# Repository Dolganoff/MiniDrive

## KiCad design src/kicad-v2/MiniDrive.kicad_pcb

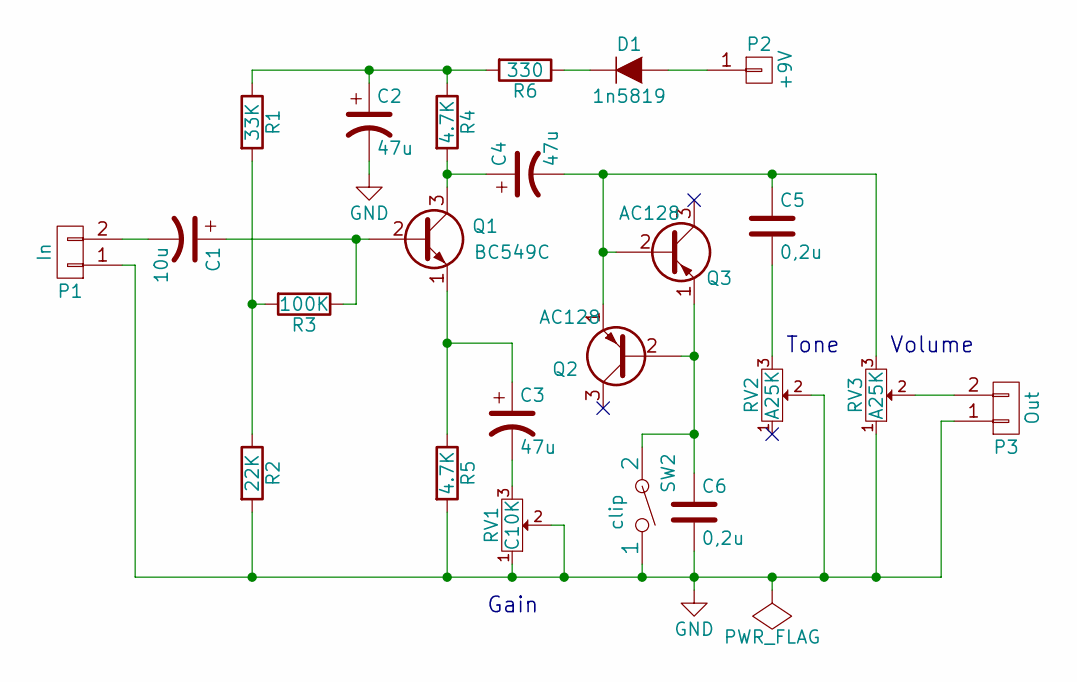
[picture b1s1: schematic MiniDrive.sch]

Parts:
C1: 10u; C1V5-LARGE_PADS
C2, C3, C4: 47u; C1V7-LARGE_PADS
C5, C6: 0,2u; C2-LARGE_PADS
D1: 1n5819; D3
P1: In; SIL-2-LARGE_PADS
P2: +9V; SolderWirePad_single_0-8mmDrill
P3: Out; SIL-2-LARGE_PADS
Q1: BC549C; TO-92_Inline_Wide
Q2, Q3: AC128; TO-18_3Pin
R1: 33K; R3-LARGE_PADS
R2: 22K; R3-LARGE_PADS
R3: 100K; R3-LARGE_PADS
R4, R5: 4.7K; R3-LARGE_PADS
R6: 330; R3-LARGE_PADS
RV1: C10K; SIL-3-LARGE_PADS
RV2, RV3: A25K; SIL-3-LARGE_PADS
SW2: clip; SIL-2-LARGE_PADS

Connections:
GND: C2.2, C6.2, P1.1, P3.1, R2.2, R5.2, RV1.1, RV1.2, RV2.2, RV3.1, SW2.1
unnamed: C1.1, Q1.2 (B), R3.1
unnamed: C1.2, P1.2
unnamed: C2.1, R1.1, R4.1, R6.2
unnamed: C3.1, Q1.1 (E), R5.1
unnamed: C3.2, RV1.3
unnamed: C4.1, Q1.3 (C), R4.2
unnamed: C4.2, C5.1, Q2.1 (E), Q3.2 (B), RV3.3
unnamed: C5.2, RV2.3
unnamed: C6.1, Q2.2 (B), Q3.1 (E), SW2.2
unnamed: D1.1 (K), R6.1
unnamed: D1.2 (A), P2.1
unnamed: P3.2, RV3.2
unnamed: R1.2, R2.1, R3.2

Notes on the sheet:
Gain
Tone
Volume

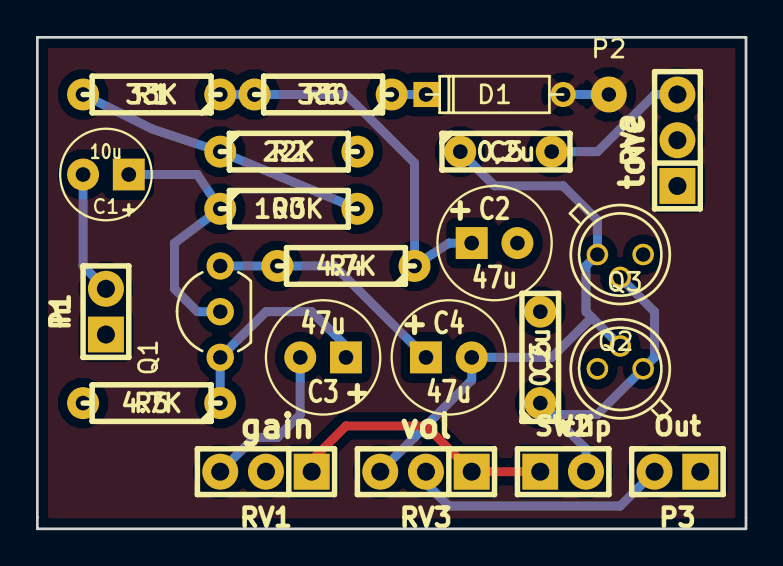
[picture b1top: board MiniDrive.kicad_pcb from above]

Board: 2 copper layers, 39.4 x 27.3 mm, 23 parts (0 on the bottom side), 14 nets.

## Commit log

2016-10-09 initial
2021-08-29 latest modifications, folder cleanup
